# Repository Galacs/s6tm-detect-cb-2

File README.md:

# S6TM Detect Carrier 2

Carrier board 2 for the detect series with LTE, TFT display, ToF and environmental sensors

## IC List

- ESP32-S3FH4R2 (Main MCU)
- TPS259472A (5A input efuse)
- 2x TPS6282 (3v3 and 3v8 SMPS)
- SIM7080G (LTE-M/NB-IoT modem)
- W25Q128JVS (16MB program storage spi flash)
- PCF85263A (RTC)
- MS5607 (Pressure sensor)
- HTU21D (Temperature and humidity)
- VL53L0X (ToF ranging sensor)
- SN65HVD230DR (CAN transceiver)
- 5x SN74LV1T125 (SIM level shifters)
- TPD3F303 (SIM ESD protection)
- WS2812B (RGB addressable led)

## Top preview

## Preview 3d render

## Pin definitions

```c
#define I2C_SDA_PIN 16
#define I2C_SCL_PIN 17

#define CAN_TX_PIN 8
#define CAN_RX_PIN 9

#define SPI_MOSI_PIN 5
#define SPI_SCLK_PIN 4
#define TFT_CS_PIN 2
#define TFT_DC_PIN 3
#define TFT_RESET_PIN 6
#define TFT_BL_PIN 7

#define TOF_INT_PIN 18

#define PM_RX_PIN 42
#define PM_TX_PIN 41
#define PM_CS_PIN 38

#define SIM_TX_PIN 35
#define SIM_RX_PIN 34
#define SIM_RTS_PIN 33
#define SIM_CTS_PIN 47
#define SIM_DTR_PIN 48
#define LTE_PWR_PIN 36

#define RGB_PIN 21
#define BTN_PIN 37

#define I_EXT_PIN 1
```

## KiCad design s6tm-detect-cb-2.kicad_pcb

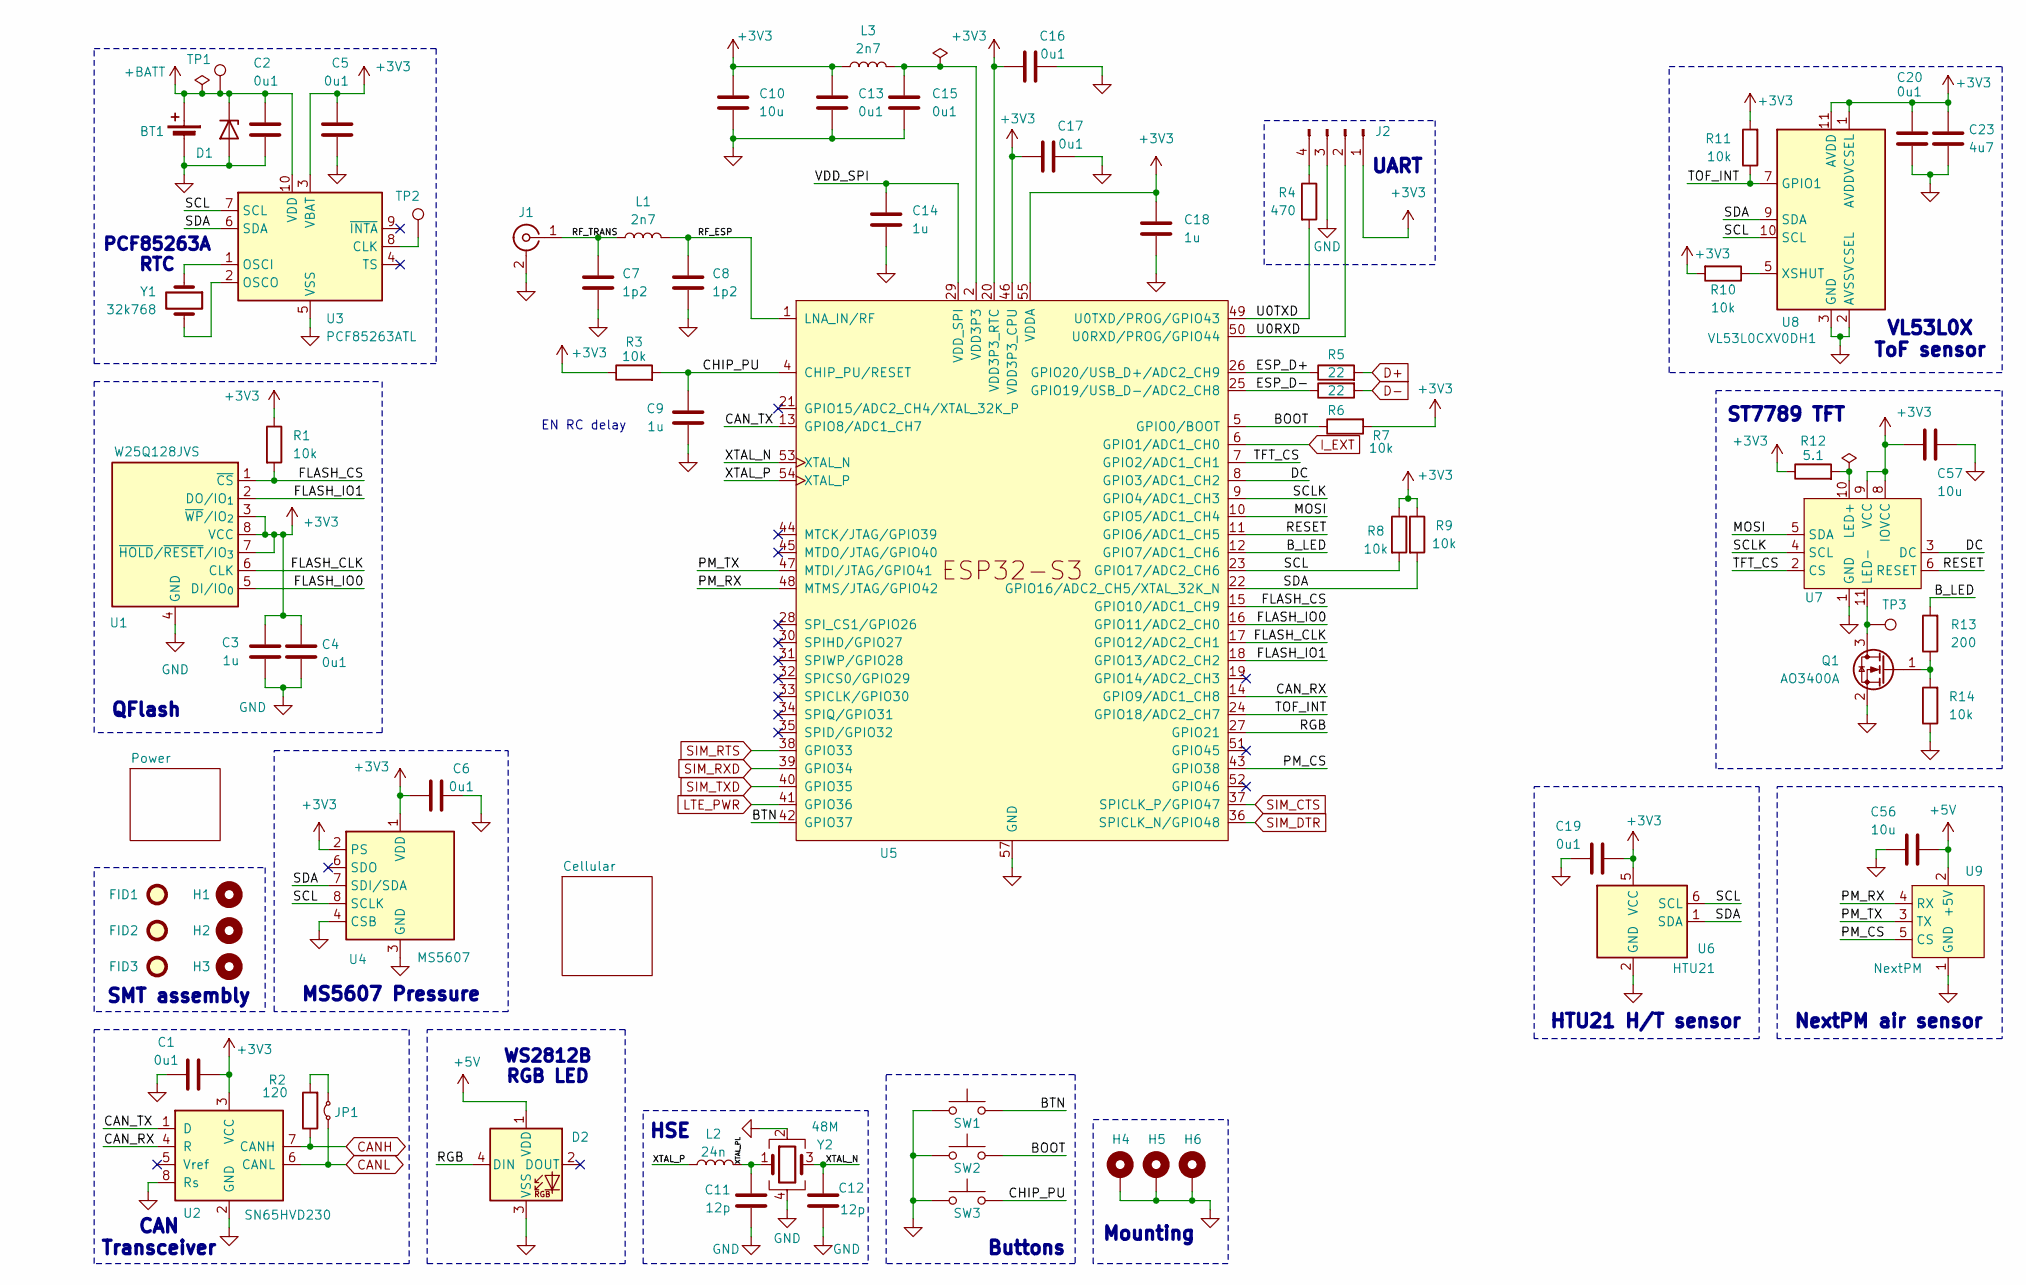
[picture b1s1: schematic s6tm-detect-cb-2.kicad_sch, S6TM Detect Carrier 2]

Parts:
BT1: Battery_Cell; BatteryHolder_MYOUNG_BS-08-B2AA016; Manufacturer Part Number BS-08-B2AA016; JLCPCB Part # C964792
C1, C2, C4, C5, C6, C13, C15, C16, C17, C19, C20: 0u1; C_0402_1005Metric; Manufacturer Part Number CL05B104KB54PNC; JLCPCB Part # C307331
C3, C9, C14, C18: 1u; C_0402_1005Metric; Manufacturer Part Number CL05A105KA5NQNC; JLCPCB Part # C52923
C7, C8: 1p2; C_0402_1005Metric; Manufacturer Part Number GJM1555C1H1R2WB01D; JLCPCB Part # C76899
C10, C56, C57: 10u; C_0603_1608Metric; Manufacturer Part Number CL10A106KP8NNNC; JLCPCB Part # C19702
C11, C12: 12p; C_0402_1005Metric; Manufacturer Part Number 0402CG120J500NT; JLCPCB Part # C1547
C23: 4u7; C_0402_1005Metric; Manufacturer Part Number CL05A475MP5NRNC; JLCPCB Part # C23733
D1: H5VU10U; Diode_DFN1006; Manufacturer Part Number H5VU10U; JLCPCB Part # C22395519
D2: WS2812B; LED_WS2812B_PLCC4_5.0x5.0mm_P3.2mm; Manufacturer Part Number WS2812B-V5/W; JLCPCB Part # C2874885
FID1, FID2, FID3: Fiducial; Fiducial_1mm_Mask2mm
H1, H2, H3: MountingHole; ToolingHole_1.152mm
H4, H5, H6: MountingHole_Pad; MountingHole_3.2mm_M3_Pad_Via
J1: Conn_Coaxial; U.FL_Hirose_U.FL-R-SMT-1_Vertical; Manufacturer Part Number U.FL-R-SMT-1(80); JLCPCB Part # C88374
J2: Conn_01x04_Pin; PinHeader_1x04_P2.54mm_Vertical
JP1: Jumper_2_Small_Bridged; SolderJumper-2_P1.3mm_Open_RoundedPad1.0x1.5mm
L1, L3: 2n7; L_0402_1005Metric; Manufacturer Part Number LQG15HS2N7S02D; JLCPCB Part # C77108
L2: 24n; L_0402_1005Metric; Manufacturer Part Number LQW15AN24NG00D; JLCPCB Part # C167472
Q1: AO3400A; SOT-23; Manufacturer Part Number AO3400A; JLCPCB Part # C20917
R1, R3, R7, R8, R9, R10, R11, R14: 10k; R_0402_1005Metric; Manufacturer Part Number 0402WGF1002TCE; JLCPCB Part # C25744
R2: 120; R_1206_3216Metric; Manufacturer Part Number 1206W4F1200T5E; JLCPCB Part # C17909
R4: 470; R_0402_1005Metric; Manufacturer Part Number 0402WGF4700TCE; JLCPCB Part # C25117
R5, R6: 22; R_0402_1005Metric; Manufacturer Part Number 0402WGF220JTCE; JLCPCB Part # C25092
R12: 5.1; R_0603_1608Metric; Manufacturer Part Number 0603WAF510KT5E; JLCPCB Part # C25197
R13: 200; R_0603_1608Metric; Manufacturer Part Number 0603WAF2000T5E; JLCPCB Part # C8218
SW1, SW2, SW3: SW_Push; SW_SPST_TS-1088-xR020; Manufacturer Part Number TS-1088-AR02016; JLCPCB Part # C720477
TP1, TP2, TP3: TestPoint; TestPoint_Pad_D2.0mm
U1: W25Q128JVS; SOIC-8_5.3x5.3mm_P1.27mm; Manufacturer Part Number W25Q128JVSIQ; JLCPCB Part # C97521
U2: SN65HVD230; SOIC-8_3.9x4.9mm_P1.27mm; Manufacturer Part Number SN65HVD230DR; JLCPCB Part # C12084
U3: PCF85263ATL; DFN-10-1EP_2.6x2.6mm_P0.5mm_EP1.3x2.2mm; Manufacturer Part Number PCF85263ATL/AX; JLCPCB Part # C2651523
U4: MS5607; LGA-8_3x5mm_P1.25mm; Manufacturer Part Number MS560702BA03-50; JLCPCB Part # C97627
U5: ESP32-S3FH4R2; QFN-56-1EP_7x7mm_P0.4mm_EP4x4mm_ThermalVias; Manufacturer Part Number ESP32-S3FH4R2; JLCPCB Part # C3013940
U6: HTU21; Texas_PWSON-N6; Manufacturer Part Number HTU21D; JLCPCB Part # C83479
U7: Hirose_FH12-12S-0.5SH_1x12-1MP_P0.50mm_Horizontal; Manufacturer Part Number FH12-12S-0.5SH(55); JLCPCB Part # C88360
U8: VL53L0CXV0DH1; ST_VL53L1x; Manufacturer Part Number VL53L0CXV0DH/1; JLCPCB Part # C91199
U9: NextPM; JST_PH_S6B-PH-K_1x06_P2.00mm_Horizontal; Manufacturer Part Number S6B-PH-K-S(LF)(SN); JLCPCB Part # C157920
Y1: 32k768; Crystal_SMD_3215-2Pin_3.2x1.5mm; Manufacturer Part Number C32346; JLCPCB Part # C32346
Y2: 48M; Crystal_SMD_2016-4Pin_2.0x1.6mm; Manufacturer Part Number R940000096; JLCPCB Part # C7206306

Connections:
+3V3: C1.1, C3.1, C4.1, C5.1, C6.2, C10.1, C13.1, C16.1, C17.1, C18.1, C19.2, C20.1, C23.1, C57.1, J2.1, L3.1, R1.1, R3.1, R7.2, R8.1, R9.1, R10.2, R11.2, R12.1, U1.3 (~WP/IO_{2}), U1.7 (~HOLD/~RESET/IO_{3}), U1.8 (VCC), U2.3 (VCC), U3.3 (VBAT), U4.1 (VDD), U4.2 (PS), U5.20 (VDD3P3_RTC), U5.46 (VDD3P3_CPU), U5.55 (VDDA), U5.56 (VDDA), U6.5 (VCC), U7.8 (IOVCC), U7.9 (VCC), U8.1 (AVDDVCSEL), U8.11 (AVDD); also elsewhere on the board
+5V: C56.2, D2.1 (VDD), U9.2 (+5V); also elsewhere on the board
+BATT: BT1.1 (+), C2.1, D1.1 (K), TP1.1 (1_1), U3.10 (VDD)
/BOOT: R7.1, SW2.2, U5.5 (GPIO0/BOOT)
/BTN: SW1.2, U5.42 (GPIO37)
/B_LED: R13.2, U5.12 (GPIO7/ADC1_CH6)
/CAN_RX: U2.4 (R), U5.14 (GPIO9/ADC1_CH8)
/CAN_TX: U2.1 (D), U5.13 (GPIO8/ADC1_CH7)
/CHIP_PU: C9.1, R3.2, SW3.2, U5.4 (CHIP_PU/RESET)
/DC: U5.8 (GPIO3/ADC1_CH2), U7.3 (DC)
/ESP_D+: R5.1, U5.26 (GPIO20/USB_D+/ADC2_CH9)
/ESP_D-: R6.1, U5.25 (GPIO19/USB_D-/ADC2_CH8)
/FLASH_CLK: U1.6 (CLK), U5.17 (GPIO12/ADC2_CH1)
/FLASH_CS: R1.2, U1.1 (~CS), U5.15 (GPIO10/ADC1_CH9)
/FLASH_IO0: U1.5 (DI/IO_{0}), U5.16 (GPIO11/ADC2_CH0)
/FLASH_IO1: U1.2 (DO/IO_{1}), U5.18 (GPIO13/ADC2_CH2)
/MOSI: U5.10 (GPIO5/ADC1_CH4), U7.5 (SDA)
/PM_CS: U5.43 (GPIO38), U9.5 (CS)
/PM_RX: U5.48 (MTMS/JTAG/GPIO42), U9.4 (RX)
/PM_TX: U5.47 (MTDI/JTAG/GPIO41), U9.3 (TX)
/RESET: U5.11 (GPIO6/ADC1_CH5), U7.6 (RESET)
/RF_ESP: C8.1, L1.2, U5.1 (LNA_IN/RF)
/RF_TRANS: C7.1, J1.1 (In), L1.1
/RGB: D2.4 (DIN), U5.27 (GPIO21)
/SCL: R8.2, U3.7 (SCL), U4.8 (SCLK), U5.23 (GPIO17/ADC2_CH6), U6.6 (SCL), U8.10 (SCL)
/SCLK: U5.9 (GPIO4/ADC1_CH3), U7.4 (SCL)
/SDA: R9.2, U3.6 (SDA), U4.7 (SDI/SDA), U5.22 (GPIO16/ADC2_CH5/XTAL_32K_N), U6.1 (SDA), U8.9 (SDA)
/TFT_CS: U5.7 (GPIO2/ADC1_CH1), U7.2 (CS)
/TOF_INT: R11.1, U5.24 (GPIO18/ADC2_CH7), U8.7 (GPIO1)
/U0RXD: J2.2, U5.50 (U0RXD/PROG/GPIO44)
/U0TXD: R4.2, U5.49 (U0TXD/PROG/GPIO43)
/VDD_SPI: C14.1, U5.29 (VDD_SPI)
/XTAL_N: C12.1, U5.53 (XTAL_N), Y2.3
/XTAL_P: L2.1, U5.54 (XTAL_P)
/XTAL_PL: C11.2, L2.2, Y2.1
CANH: R2.1, U2.7 (CANH); also elsewhere on the board
CANL: JP1.1 (A), U2.6 (CANL); also elsewhere on the board
D+: R5.2; also elsewhere on the board
D-: R6.2; also elsewhere on the board
EPAD: U6.7 (DAP)
GND: BT1.2 (-), C1.2, C2.2, C3.2, C4.2, C5.2, C6.1, C7.2, C8.2, C9.2, C10.2, C11.1, C12.2, C13.2, C14.2, C15.2, C16.2, C17.2, C18.2, C19.1, C20.2, C23.2, C56.1, C57.2, D1.2 (A), D2.3 (VSS), H4.1 (1_1), H5.1 (1_1), H6.1 (1_1), J1.2 (Ext), J2.3, Q1.2 (S), R14.1, SW1.1, SW2.1, SW3.1, U1.4 (GND), U2.2 (GND), U2.8 (Rs), U3.5 (VSS), U4.3 (GND), U4.4 (CSB), U4.5 (CSB), U5.57 (GND), U6.2 (GND), U7.1 (GND), U7.12 (GND), U7.MP (GND), U8.2 (AVSSVCSEL), U8.3 (GND), U8.4 (GND), U8.6 (GND), U8.12 (GND), U9.1 (GND), U9.6 (GND), Y2.2, Y2.4; also elsewhere on the board
I_EXT: U5.6 (GPIO1/ADC1_CH0); also elsewhere on the board
LTE_PWR: U5.41 (GPIO36); also elsewhere on the board
unnamed: J2.4, R4.1
unnamed: JP1.2 (B), R2.2
unnamed: Q1.3 (D), TP3.1 (1_1), U7.11 (LED-)
unnamed: Q1.1 (G), R13.1, R14.2
unnamed: TP2.1 (1_1), U3.8 (CLK)
unnamed: U3.1 (OSCI), Y1.1
unnamed: U3.2 (OSCO), Y1.2
unnamed: R12.2, U7.10 (LED+)
unnamed: R10.1, U8.5 (XSHUT)
SIM_CTS: U5.37 (SPICLK_P/GPIO47); also elsewhere on the board
SIM_DTR: U5.36 (SPICLK_N/GPIO48); also elsewhere on the board
SIM_RTS: U5.38 (GPIO33); also elsewhere on the board
SIM_RXD: U5.39 (GPIO34); also elsewhere on the board
SIM_TXD: U5.40 (GPIO35); also elsewhere on the board
VDD3P3: C15.1, L3.2, U5.2 (VDD3P3), U5.3 (VDD3P3)

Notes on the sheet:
WS2812B RGB LED
NextPM air sensor
ST7789 TFT
HTU21 H/T sensor
HSE
CAN Transceiver
QFlash
VL53L0X ToF sensor
PCF85263A RTC
SMT assembly
MS5607 Pressure
EN RC delay
UART
Mounting
Buttons

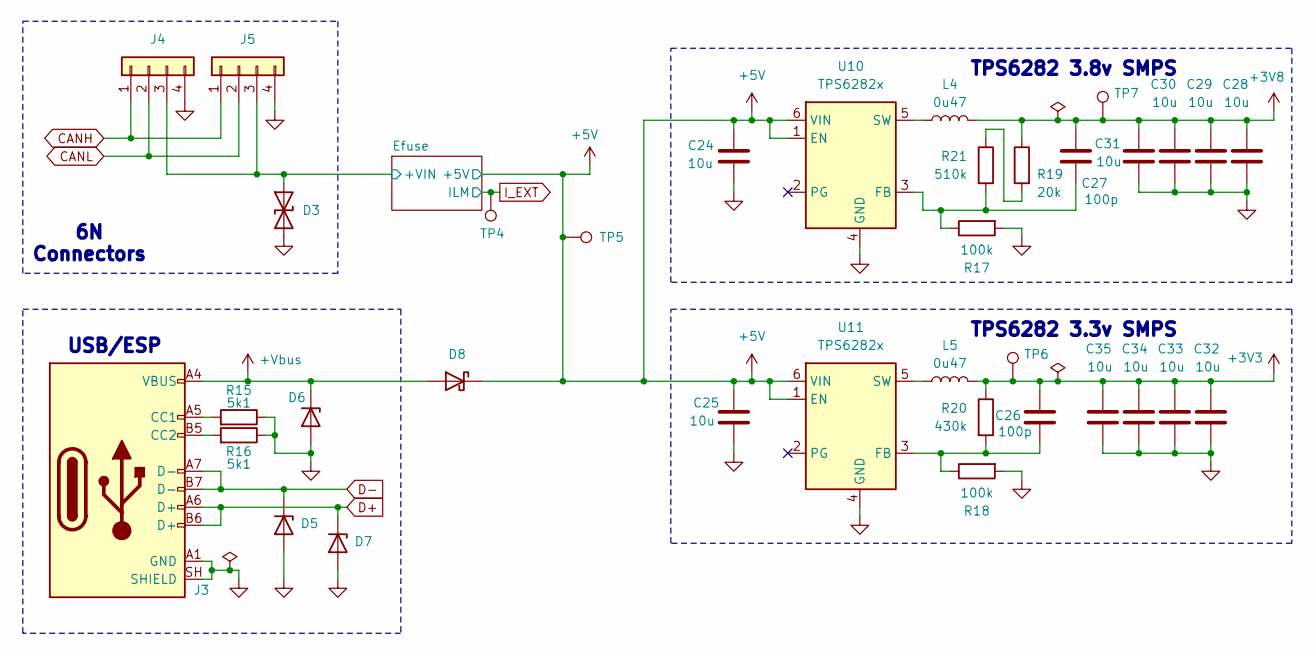
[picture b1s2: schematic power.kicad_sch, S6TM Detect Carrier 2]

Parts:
C24, C25, C28, C29, C30, C31, C32, C33, C34, C35: 10u; C_0603_1608Metric; Manufacturer Part Number CL10A106KP8NNNC; JLCPCB Part # C19702
C26, C27: 100p; C_0402_1005Metric; Manufacturer Part Number 0402CG101J500NT; JLCPCB Part # C1546
D3: SMBJ6.0CA; D_SMB; Manufacturer Part Number SMBJ6.0CA; JLCPCB Part # C2925451
D5, D6, D7: H5VU10U; Diode_DFN1006; Manufacturer Part Number H5VU10U; JLCPCB Part # C22395519
D8: D_Schottky; D_SMA; Manufacturer Part Number SS54; JLCPCB Part # C22452
J3: USB_C_Receptacle_USB2.0_14P; USB_C_Receptacle_HRO_TYPE-C-31-M-12; Manufacturer Part Number TYPE-C16PIN; JLCPCB Part # C393939
J4, J5: Conn_01x04; JST_XH_S4B-XH-A-1_1x04_P2.50mm_Horizontal; Manufacturer Part Number S4B-XH-A-1(LF)(SN); JLCPCB Part # C163037
L4, L5: 0u47; TDK_TFM201610ALC; Manufacturer Part Number TFM201610GHM-R47MTAA; JLCPCB Part # C89446
R15, R16: 5k1; R_0402_1005Metric; Manufacturer Part Number 0402WGF5101TCE; JLCPCB Part # C25905
R17, R18: 100k; R_0402_1005Metric; Manufacturer Part Number 0402WGF1003TCE; JLCPCB Part # C25741
R19: 20k; R_0402_1005Metric; Manufacturer Part Number 0402WGF2002TCE; JLCPCB Part # C25765
R20: 430k; R_0603_1608Metric; Manufacturer Part Number 0603WAF4303T5E; JLCPCB Part # C25969
R21: 510k; R_0603_1608Metric; Manufacturer Part Number 0603WAF5103T5E; JLCPCB Part # C23192
TP4, TP5, TP6, TP7: TestPoint; TestPoint_Pad_D2.0mm
U10, U11: TPS6282x; Texas_VSON-6_1.5x1.5mm_P0.5mm_DMQ0006A; Manufacturer Part Number TPS62825DMQR; JLCPCB Part # C2650334

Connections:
+3V3: C26.1, C32.1, C33.1, C34.1, C35.1, L5.2, R20.1, TP6.1 (1_1); also elsewhere on the board
+3V8: C27.1, C28.1, C29.1, C30.1, C31.1, L4.2, R19.1, TP7.1 (1_1); also elsewhere on the board
+5V: C24.1, C25.1, D8.1 (K), TP5.1 (1_1), U10.1 (EN), U10.6 (VIN), U11.1 (EN), U11.6 (VIN); also elsewhere on the board
+Vbus: D6.1 (K), D8.2 (A), J3.A4 (VBUS), J3.A9 (VBUS), J3.B4 (VBUS), J3.B9 (VBUS)
/Power/Efuse/+VIN: D3.1 (A1), J4.3, J5.3; also elsewhere on the board
CANH: J4.1, J5.1; also elsewhere on the board
CANL: J4.2, J5.2; also elsewhere on the board
D+: D7.1 (K), J3.A6 (D+), J3.B6 (D+); also elsewhere on the board
D-: D5.1 (K), J3.A7 (D-), J3.B7 (D-); also elsewhere on the board
GND: C24.2, C25.2, C28.2, C29.2, C30.2, C31.2, C32.2, C33.2, C34.2, C35.2, D3.2 (A2), D5.2 (A), D6.2 (A), D7.2 (A), J3.A1 (GND), J3.A12 (GND), J3.B1 (GND), J3.B12 (GND), J3.SH (SHIELD), J4.4, J5.4, R15.1, R16.1, R17.2, R18.2, U10.4 (GND), U11.4 (GND); also elsewhere on the board
I_EXT: TP4.1 (1_1); also elsewhere on the board
unnamed: J3.A5 (CC1), R15.2
unnamed: J3.B5 (CC2), R16.2
unnamed: R19.2, R21.1
unnamed: C27.2, R17.1, R21.2, U10.3 (FB)
unnamed: L4.1, U10.5 (SW)
unnamed: C26.2, R18.1, R20.2, U11.3 (FB)
unnamed: L5.1, U11.5 (SW)

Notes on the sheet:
TPS6282 3.3v SMPS
TPS6282 3.8v SMPS
6N Connectors
USB/ESP

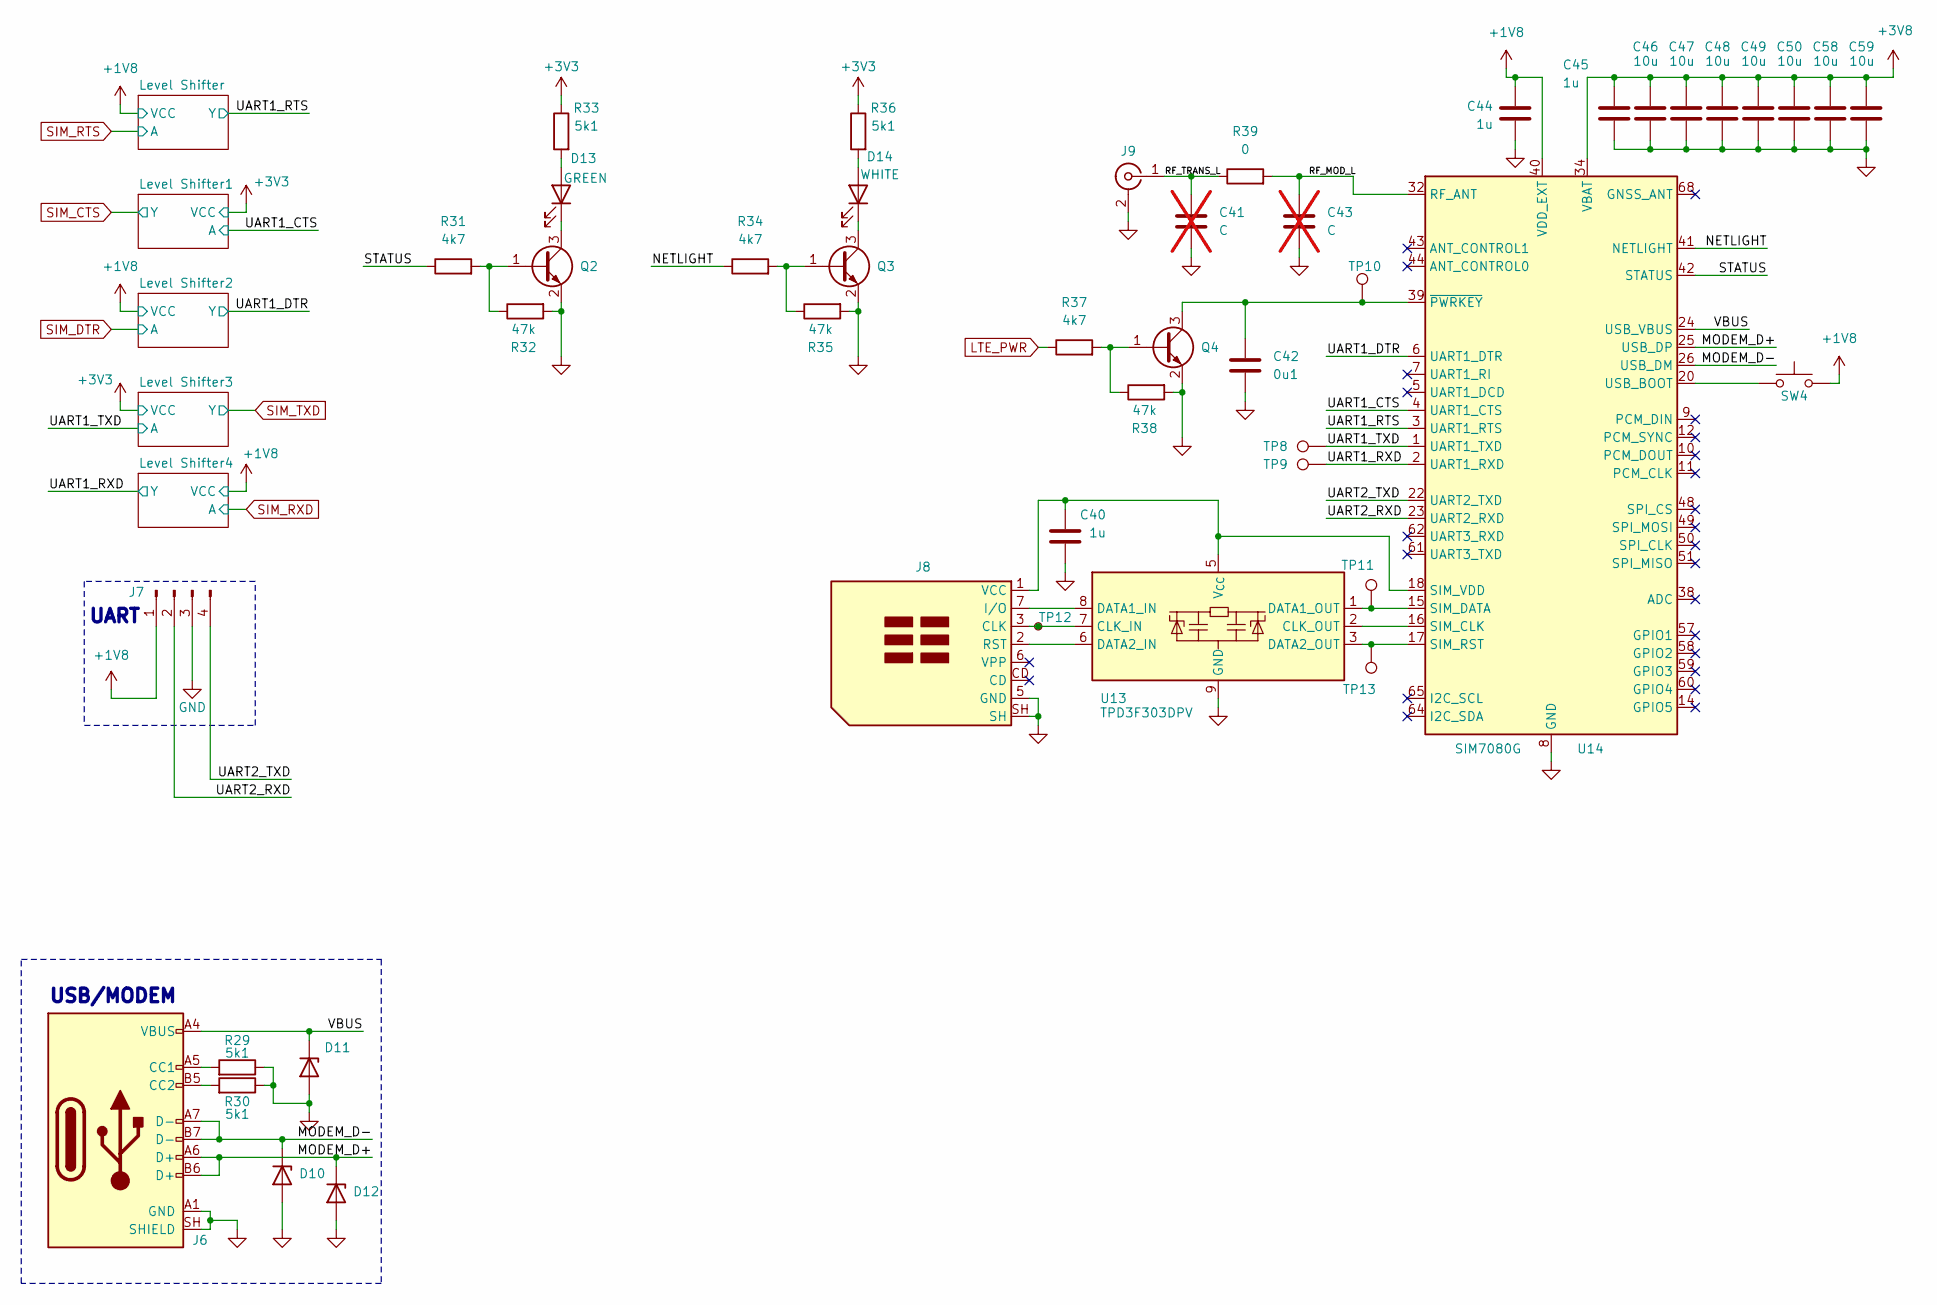
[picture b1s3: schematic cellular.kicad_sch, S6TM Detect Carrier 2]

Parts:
C40, C44, C45: 1u; C_0402_1005Metric; Manufacturer Part Number CL05A105KA5NQNC; JLCPCB Part # C52923
C41, C43: C; C_0402_1005Metric; not fitted
C42: 0u1; C_0402_1005Metric; Manufacturer Part Number CL05B104KB54PNC; JLCPCB Part # C307331
C46, C47, C48, C49, C50, C58, C59: 10u; C_0603_1608Metric; Manufacturer Part Number CL10A106KP8NNNC; JLCPCB Part # C19702
D10, D11, D12: H5VU10U; Diode_DFN1006; Manufacturer Part Number H5VU10U; JLCPCB Part # C22395519
D13: GREEN; LED_0805_2012Metric; Manufacturer Part Number KT-0805G; JLCPCB Part # C2297
D14: WHITE; LED_0603_1608Metric; Manufacturer Part Number KT-0603W; JLCPCB Part # C2290
J6: USB_C_Receptacle_USB2.0_14P; USB_C_Receptacle_HRO_TYPE-C-31-M-12; Manufacturer Part Number TYPE-C16PIN; JLCPCB Part # C393939
J7: Conn_01x04_Pin; PinHeader_1x04_P2.54mm_Vertical
J8: SIM_Card_Shielded; nanoSIM_Hinged_CUI_NSIM-2-C; Manufacturer Part Number SMN-305-ARP7; JLCPCB Part # C720512
J9: Conn_Coaxial; U.FL_Hirose_U.FL-R-SMT-1_Vertical; Manufacturer Part Number U.FL-R-SMT-1(80); JLCPCB Part # C88374
Q2, Q3, Q4: MMBT3904; SOT-23; Manufacturer Part Number MMBT3904(RANGE:100-300); JLCPCB Part # C20526
R29, R30, R33, R36: 5k1; R_0402_1005Metric; Manufacturer Part Number 0402WGF5101TCE; JLCPCB Part # C25905
R31, R34, R37: 4k7; R_0402_1005Metric; Manufacturer Part Number 0402WGF4701TCE; JLCPCB Part # C25900
R32, R35, R38: 47k; R_0402_1005Metric; Manufacturer Part Number 0402WGF4702TCE; JLCPCB Part # C25792
R39: 0; R_0402_1005Metric; Manufacturer Part Number 0402WGF0000TCE; JLCPCB Part # C17168
SW4: SW_Push; SW_SPST_TS-1088-xR020; Manufacturer Part Number TS-1088-AR02016; JLCPCB Part # C720477
TP8, TP9, TP10, TP11, TP12, TP13: TestPoint; TestPoint_Pad_D2.0mm
U13: TPD3F303DPV; Texas_R-PUSON-N8_USON-8-1EP_1.6x2.1mm_P0.5mm_EP0.4x1.7mm; Manufacturer Part Number TPD3F303DPVR; JLCPCB Part # C2865991
U14: SIM7080G; SIMCom_SIM7080G; Manufacturer Part Number C2943992; JLCPCB Part # C2943992

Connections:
+1V8: C44.2, J7.1, SW4.2, U14.40 (VDD_EXT); also elsewhere on the board
+3V3: R33.1, R36.1; also elsewhere on the board
+3V8: C45.2, C46.1, C47.1, C48.1, C49.1, C50.1, C58.1, C59.1, U14.34 (VBAT), U14.35 (VBAT); also elsewhere on the board
/Cellular/MODEM_D+: D12.1 (K), J6.A6 (D+), J6.B6 (D+), U14.25 (USB_DP)
/Cellular/MODEM_D-: D10.1 (K), J6.A7 (D-), J6.B7 (D-), U14.26 (USB_DM)
/Cellular/NETLIGHT: R34.1, U14.41 (NETLIGHT)
/Cellular/RF_MOD_L: C43.1, R39.2, U14.32 (RF_ANT)
/Cellular/RF_TRANS_L: C41.1, J9.1 (In), R39.1
/Cellular/STATUS: R31.1, U14.42 (STATUS)
/Cellular/UART1_CTS: U14.4 (UART1_CTS); also elsewhere on the board
/Cellular/UART1_DTR: U14.6 (UART1_DTR); also elsewhere on the board
/Cellular/UART1_RTS: U14.3 (UART1_RTS); also elsewhere on the board
/Cellular/UART1_RXD: TP9.1 (1_1), U14.2 (UART1_RXD); also elsewhere on the board
/Cellular/UART1_TXD: TP8.1 (1_1), U14.1 (UART1_TXD); also elsewhere on the board
/Cellular/UART2_RXD: J7.2, U14.23 (UART2_RXD)
/Cellular/UART2_TXD: J7.4, U14.22 (UART2_TXD)
/Cellular/VBUS: D11.1 (K), J6.A4 (VBUS), J6.A9 (VBUS), J6.B4 (VBUS), J6.B9 (VBUS), U14.24 (USB_VBUS)
GND: C40.1, C41.2, C42.1, C43.2, C44.1, C45.1, C46.2, C47.2, C48.2, C49.2, C50.2, C58.2, C59.2, D10.2 (A), D11.2 (A), D12.2 (A), J6.A1 (GND), J6.A12 (GND), J6.B1 (GND), J6.B12 (GND), J6.SH (SHIELD), J7.3, J8.5 (GND), J8.SH, J9.2 (Ext), Q2.2 (E), Q3.2 (E), Q4.2 (E), R29.1, R30.1, R32.2, R35.2, R38.2, U13.9 (GND), U14.8 (GND), U14.13 (GND), U14.19 (GND), U14.21 (GND), U14.27 (GND), U14.30 (GND), U14.31 (GND), U14.33 (GND), U14.36 (GND), U14.37 (GND), U14.45 (GND), U14.63 (GND), U14.66 (GND), U14.67 (GND), U14.69 (GND), U14.70 (GND), U14.71 (GND), U14.72 (GND), U14.73 (GND), U14.74 (GND), U14.75 (GND), U14.76 (GND), U14.77 (GND); also elsewhere on the board
LTE_PWR: R37.1; also elsewhere on the board
unnamed: D13.2 (A), R33.2
unnamed: D13.1 (K), Q2.3 (C)
unnamed: D14.2 (A), R36.2
unnamed: D14.1 (K), Q3.3 (C)
unnamed: J6.A5 (CC1), R29.2
unnamed: J6.B5 (CC2), R30.2
unnamed: J8.3 (CLK), TP12.1 (1_1), U13.7 (CLK_IN)
unnamed: J8.7 (I/O), U13.8 (DATA1_IN)
unnamed: J8.2 (RST), U13.6 (DATA2_IN)
unnamed: C40.2, J8.1 (VCC), U13.5 (V_{CC}), U14.18 (SIM_VDD)
unnamed: Q2.1 (B), R31.2, R32.1
unnamed: Q3.1 (B), R34.2, R35.1
unnamed: Q4.1 (B), R37.2, R38.1
unnamed: C42.2, Q4.3 (C), TP10.1 (1_1), U14.39 (~PWRKEY)
unnamed: U13.2 (CLK_OUT), U14.16 (SIM_CLK)
unnamed: TP11.1 (1_1), U13.1 (DATA1_OUT), U14.15 (SIM_DATA)
unnamed: TP13.1 (1_1), U13.3 (DATA2_OUT), U14.17 (SIM_RST)
unnamed: SW4.1, U14.20 (USB_BOOT)

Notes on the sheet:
UART
USB/MODEM

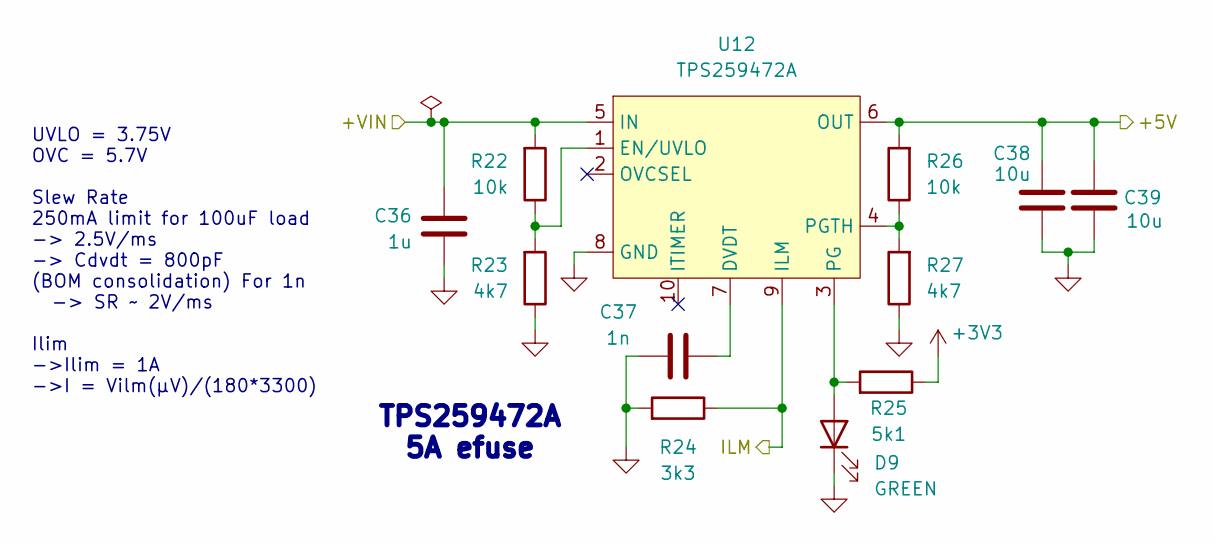
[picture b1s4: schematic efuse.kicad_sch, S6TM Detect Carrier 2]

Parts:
C36: 1u; C_0402_1005Metric; Manufacturer Part Number CL05A105KA5NQNC; JLCPCB Part # C52923
C37: 1n; C_0402_1005Metric; Manufacturer Part Number 0402B102K500NT; JLCPCB Part # C1523
C38, C39: 10u; C_0603_1608Metric; Manufacturer Part Number CL10A106KP8NNNC; JLCPCB Part # C19702
D9: GREEN; LED_0805_2012Metric; Manufacturer Part Number KT-0805G; JLCPCB Part # C2297
R22, R26: 10k; R_0402_1005Metric; Manufacturer Part Number 0402WGF1002TCE; JLCPCB Part # C25744
R23, R27: 4k7; R_0402_1005Metric; Manufacturer Part Number 0402WGF4701TCE; JLCPCB Part # C25900
R24: 3k3; R_0402_1005Metric; Manufacturer Part Number 0402WGF3301TCE; JLCPCB Part # C25890
R25: 5k1; R_0402_1005Metric; Manufacturer Part Number 0402WGF5101TCE; JLCPCB Part # C25905
U12: TPS259472A; Texas_RPW0010A_VQFN-HR-10_2x2mm_P0.5mm; Manufacturer Part Number TPS259472ARPWR; JLCPCB Part # C3662789

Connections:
+3V3: R25.1; also elsewhere on the board
+5V: C38.1, C39.1, R26.2, U12.6 (OUT); also elsewhere on the board
/Power/Efuse/+VIN: C36.2, R22.2, U12.5 (IN); also elsewhere on the board
GND: C36.1, C37.2, C38.2, C39.2, D9.1 (K), R23.1, R24.2, R27.1, U12.8 (GND); also elsewhere on the board
I_EXT: R24.1, U12.9 (ILM); also elsewhere on the board
unnamed: D9.2 (A), R25.2, U12.3 (PG)
unnamed: C37.1, U12.7 (DVDT)
unnamed: R22.1, R23.2, U12.1 (EN/UVLO)
unnamed: R26.1, R27.2, U12.4 (PGTH)

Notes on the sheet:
TPS259472A 5A efuse
UVLO = 3.75V OVC = 5.7V Slew Rate 250mA limit for 100uF load -> 2.5V/ms -> Cdvdt = 800pF (BOM consolidation) For 1n -> SR ~ 2V/ms Ilim ->Ilim = 1A ->I = Vilm(µV)/(180*3300)

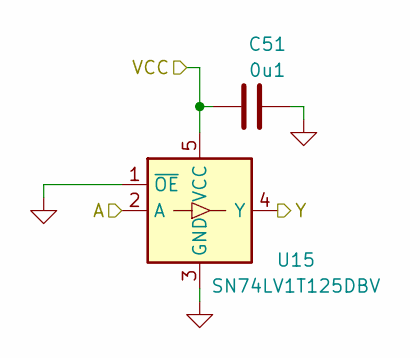
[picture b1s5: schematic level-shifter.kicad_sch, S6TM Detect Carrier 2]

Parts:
C51: 0u1; C_0402_1005Metric; Manufacturer Part Number CL05B104KB54PNC; JLCPCB Part # C307331
U15: SN74LV1T125DBV; SOT-23-5; Manufacturer Part Number SN74LV1T125DBVR; JLCPCB Part # C473338

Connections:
+1V8: C51.1, U15.5 (VCC); also elsewhere on the board
/Cellular/UART1_RTS: U15.4 (Y); also elsewhere on the board
GND: C51.2, U15.1 (~OE), U15.3 (GND); also elsewhere on the board
SIM_RTS: U15.2 (A); also elsewhere on the board

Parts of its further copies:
C52, C53, C54, C55: 0u1; C_0402_1005Metric; Manufacturer Part Number CL05B104KB54PNC; JLCPCB Part # C307331
U16, U17, U18, U19: SN74LV1T125DBV; SOT-23-5; Manufacturer Part Number SN74LV1T125DBVR; JLCPCB Part # C473338

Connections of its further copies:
+1V8: C53.1, C55.1, U17.5 (VCC), U19.5 (VCC); also elsewhere on the board
+3V3: C52.1, C54.1, U16.5 (VCC), U18.5 (VCC); also elsewhere on the board
/Cellular/UART1_CTS: U16.2 (A); also elsewhere on the board
/Cellular/UART1_DTR: U17.4 (Y); also elsewhere on the board
/Cellular/UART1_RXD: U19.4 (Y); also elsewhere on the board
/Cellular/UART1_TXD: U18.2 (A); also elsewhere on the board
GND: C52.2, C53.2, C54.2, C55.2, U16.1 (~OE), U16.3 (GND), U17.1 (~OE), U17.3 (GND), U18.1 (~OE), U18.3 (GND), U19.1 (~OE), U19.3 (GND); also elsewhere on the board
SIM_CTS: U16.4 (Y); also elsewhere on the board
SIM_DTR: U17.2 (A); also elsewhere on the board
SIM_RXD: U19.2 (A); also elsewhere on the board
SIM_TXD: U18.4 (Y); also elsewhere on the board

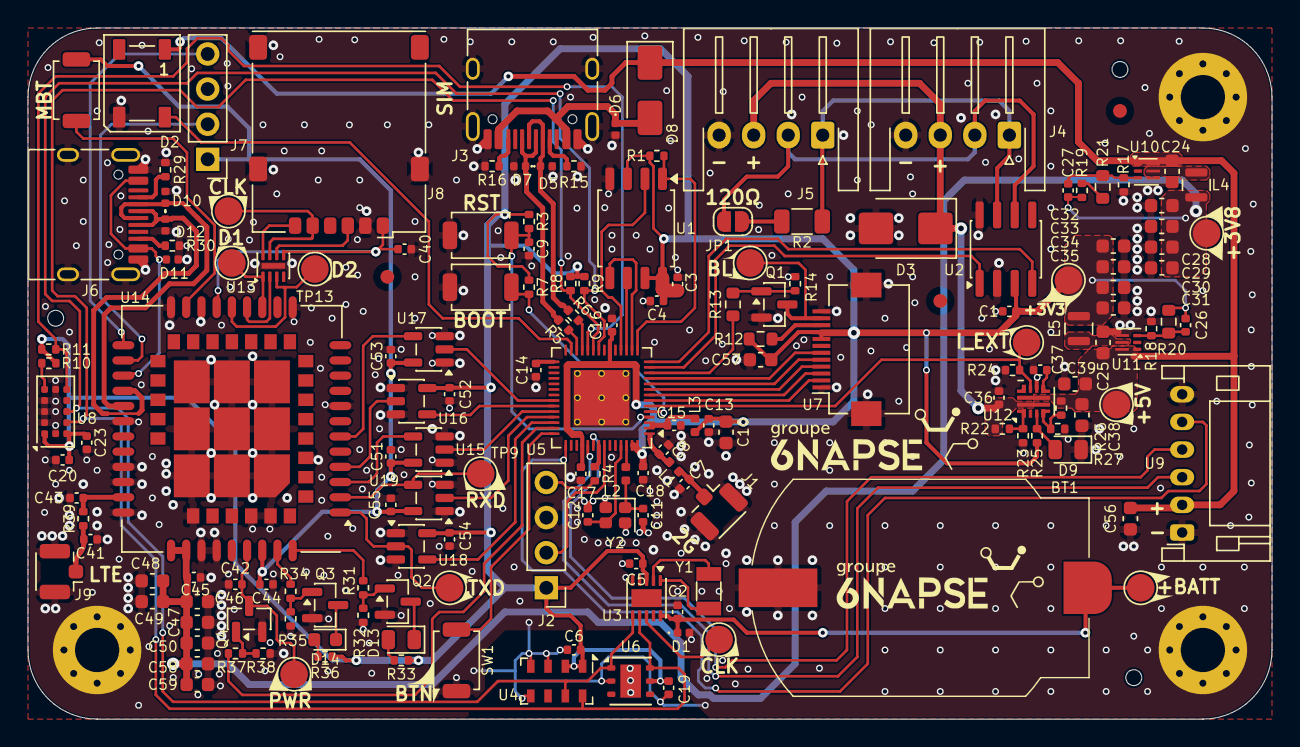
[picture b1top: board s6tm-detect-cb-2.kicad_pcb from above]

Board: 4 copper layers, 90.0 x 50.0 mm, 175 parts (0 on the bottom side), 104 nets.

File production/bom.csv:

Designator,Footprint,Quantity,Value,LCSC Part #
BT1,BatteryHolder_MYOUNG_BS-08-B2AA016,1,Battery_Cell,C964792
"C1, C13, C15, C16, C17, C19, C2, C20, C4, C42, C5, C51, C52, C53, C54, C55, C6",0402,17,0u1,C307331
"C10, C24, C25, C28, C29, C30, C31, C32, C33, C34, C35, C38, C39, C46, C47, C48, C49, C50, C56, C57, C58, C59",0603,22,10u,C19702
"C11, C12",0402,2,12p,C1547
"C14, C18, C3, C36, C40, C44, C45, C9",0402,8,1u,C52923
C23,0402,1,4u7,C23733
"C26, C27",0402,2,100p,C1546
C37,0402,1,1n,C1523
"C7, C8",0402,2,1p2,C76899
"D1, D10, D11, D12, D5, D6, D7",Diode_DFN1006,7,H5VU10U,C22395519
"D13, D9",0805,2,GREEN,C2297
D14,0603,1,WHITE,C2290
D2,LED_WS2812B_PLCC4_5.0x5.0mm_P3.2mm,1,WS2812B,C2874885
D3,D_SMB,1,SMBJ6.0CA,C2925451
D8,D_SMA,1,D_Schottky,C22452
"J1, J9",U.FL_Hirose_U.FL-R-SMT-1_Vertical,2,Conn_Coaxial,C88374
"J3, J6",USB_C_Receptacle_HRO_TYPE-C-31-M-12,2,USB_C_Receptacle_USB2.0_14P,C393939
J8,nanoSIM_Hinged_CUI_NSIM-2-C,1,SIM_Card_Shielded,C720512
"L1, L3",0402,2,2n7,C77108
L2,0402,1,24n,C167472
"L4, L5",TDK_TFM201610ALC,2,0u47,C89446
Q1,SOT-23,1,AO3400A,C20917
"Q2, Q3, Q4",SOT-23,3,MMBT3904,C20526
"R1, R10, R11, R14, R22, R26, R3, R7, R8, R9",0402,10,10k,C25744
R12,0603,1,5.1,C25197
R13,0603,1,200,C8218
"R15, R16, R25, R29, R30, R33, R36",0402,7,5k1,C25905
"R17, R18",0402,2,100k,C25741
R19,0402,1,20k,C25765
R2,1206,1,120,C17909
R20,0603,1,430k,C25969
R21,0603,1,510k,C23192
"R23, R27, R31, R34, R37",0402,5,4k7,C25900
R24,0402,1,3k3,C25890
"R32, R35, R38",0402,3,47k,C25792
R39,0402,1,0,C17168
R4,0402,1,470,C25117
"R5, R6",0402,2,22,C25092
"SW1, SW2, SW3, SW4",SW_SPST_TS-1088-xR020,4,SW_Push,C720477
U1,SOIC-8_5.3x5.3mm_P1.27mm,1,W25Q128JVS,C97521
"U10, U11",Texas_VSON-6_1.5x1.5mm_P0.5mm_DMQ0006A,2,TPS6282x,C2650334
U12,Texas_RPW0010A_VQFN-HR-10_2x2mm_P0.5mm,1,TPS259472A,C3662789
U13,Texas_R-PUSON-N8_USON-8-1EP_1.6x2.1mm_P0.5mm_EP0.4x1.7mm,1,TPD3F303DPV,C2865991
U14,SIMCom_SIM7080G,1,SIM7080G,C2943992
"U15, U16, U17, U18, U19",SOT-23-5,5,SN74LV1T125DBV,C473338
U2,SOIC-8_3.9x4.9mm_P1.27mm,1,SN65HVD230,C12084
U3,DFN-10-1EP_2.6x2.6mm_P0.5mm_EP1.3x2.2mm,1,PCF85263ATL,C2651523
U4,LGA-8_3x5mm_P1.25mm,1,MS5607,C97627
U5,QFN-56-1EP_7x7mm_P0.4mm_EP4x4mm_ThermalVias,1,ESP32-S3FH4R2,C3013940
U6,Texas_PWSON-N6,1,HTU21,C83479
U7,Hirose_FH12-12S-0.5SH_1x12-1MP_P0.50mm_Horizontal,1,~,C88360
U8,ST_VL53L1x,1,VL53L0CXV0DH1,C91199
U9,JST_PH_S6B-PH-K_1x06_P2.00mm_Horizontal,1,NextPM,C157920
Y1,Crystal_SMD_3215-2Pin_3.2x1.5mm,1,32k768,C32346
Y2,Crystal_SMD_2016-4Pin_2.0x1.6mm,1,48M,C7206306
